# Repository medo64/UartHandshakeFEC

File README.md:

[UART w/Handshake Framework Expansion Card](https://medo64.com/uarthandshakefec/)
=================================================================================

This Framework laptop expansion card will show up on your system as a serial
device and allow for a non-isolated serial UART communication up to 3 Mbaud
baud rate with all handshake signals exposed.

Please note that this card is not using RS-232 but TTL (either 3.3V or 5V)
voltage levels (depending on the solder-jumper position).

## UART Pinout

To connect to this board, one has to use a 7-pin JST XH connector. The following
table represents the pinout, pin 1 being on the left as looking into the
expansion card.

| # | Ref  | Description                        |
|--:|:----:|------------------------------------|
| 1 | CTS# | Clear To Send Control Input        |
| 2 | DSR# | Data Set Ready Control Input       |
| 3 | RXD  | Receiving  Data Input.             |
| 4 | GND  | Ground supply                      |
| 5 | TXD  | Transmit Data Output               |
| 6 | DTR# | Data Terminal Ready Control Output |
| 7 | RTS# | Request to Send Control Output     |

As power consumption is low, wires can be almost any AWG. I would recommend
using 24 AWG wire 0.25 mm² as they allow for greater compatibility with other
connectors.

## Supported Speeds

This board employs the FT232R as its UART chip, and consequently, it supports
all the baud rates this chip [can handle](https://ftdichip.com/Documents/AppNotes/AN232B-05_BaudRates.pdf).
The table below lists the standard baud rates.

| Baud rate |    Actual | Error |    Divisor |
|----------:|----------:|------:|-----------:|
|       300 |       300 | 0.00% |  10000.000 |
|       600 |       600 | 0.00% |   5000.000 |
|     1,200 |     1,200 | 0.00% |   2500.000 |
|     1,800 |     1,800 | 0.00% |   1666.625 |
|     2,400 |     2,400 | 0.00% |   1250.000 |
|     4,800 |     4,800 | 0.00% |    625.000 |
|     7,200 |     7,201 | 0.01% |    416.625 |
|     9,600 |     9,600 | 0.00% |    312.500 |
|    14,400 |    14,406 | 0.04% |    208.250 |
|    19,200 |    19,200 | 0.00% |    156.250 |
|    28,800 |    28,812 | 0.04% |    104.125 |
|    38,400 |    38,400 | 0.00% |     78.125 |
|    57,600 |    57,692 | 0.16% |     52.000 |
|   115,200 |   115,385 | 0.16% |     26.000 |
|   230,400 |   230,769 | 0.16% |     13.000 |
|   460,800 |   461,538 | 0.16% |      6.500 |
|   921,600 |   923,077 | 0.16% |      3.250 |
| 1,000,000 | 1,000,000 | 0.00% |      3.000 |

While the UART chip does support baud rates up to 3 Mbaud, granularity of such
rates is severely limited.

---
*You can check my blog and other projects at [www.medo64.com](https://www.medo64.com/electronics/).*

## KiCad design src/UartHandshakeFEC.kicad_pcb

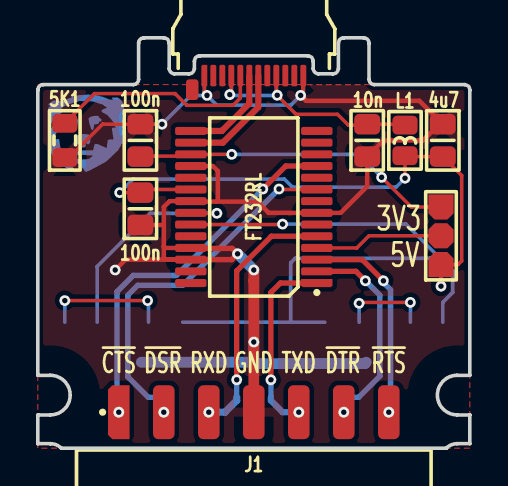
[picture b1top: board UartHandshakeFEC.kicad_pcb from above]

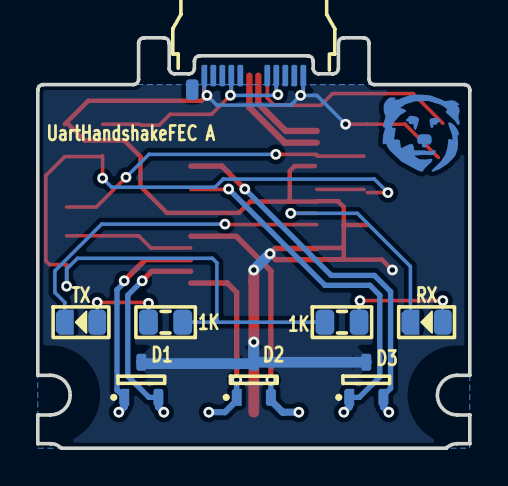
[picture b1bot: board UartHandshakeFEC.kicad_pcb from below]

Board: 2 copper layers, 24.0 x 22.8 mm, 18 parts (8 on the bottom side), 18 nets.

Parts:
C1: 10n; C (0805)
C2, C3: 100n; C (0805)
C4: 4u7; C (0805)
D1, D2, D3: SM05T1G; D TVS SM05T1G (SOT23-3)
DS1: RX; DS (0805)
DS2: TX; DS (0805)
ICON: Medo64; ICON Medo64
J1: B7B-XH-A; J JST XH Edge [UART] (7w)
JP1: Jumper; JP Dual (1205)
L1: 600R; L (0805)
P1: 105444-0001; P USB C 3.2 Edge (24w)
R1, R2: 1K; R (0805)
R3: 5K1; R (0805)
U1: FT232RL; U Transciever UART FT232RL (SSOP-28)

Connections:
3V3: C3.2, JP1.3, U1.17
5V: C2.2, C4.2, JP1.1, L1.1, R1.1, R2.1, U1.20
A_CC: P1.A5, R3.2
CTS#: D3.2, J1.1, U1.11
DSR#: D3.1, J1.2, U1.9
DTR#: D1.2, J1.6, U1.2
GND: C1.1, C2.1, C3.1, C4.1, D1.3, D2.3, D3.3, J1.4, P1.A1, P1.A12, P1.B01, P1.B12, R3.1, U1.7, U1.18, U1.21, U1.25, U1.26
LED_RXD: DS1.1, U1.22
LED_RXD': DS1.2, R1.2
LED_TXD: DS2.1, U1.23
LED_TXD': DS2.2, R2.2
RTS#: D1.1, J1.7, U1.3
RXD: D2.2, J1.3, U1.5
TXD: D2.1, J1.5, U1.1
USB_DM: P1.A7, U1.16
USB_DP: P1.A6, U1.15
USB_Vin: C1.2, L1.2, P1.A4, P1.A9, P1.B04, P1.B09
Vio: JP1.2, U1.4

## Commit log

2023-11-05 Updated pinout to match cisco-style pin order
2023-11-13 Refactoring LEDs to bottom
